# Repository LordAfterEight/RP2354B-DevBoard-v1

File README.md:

# RP2354B-DevBoard-v1
Repository for my first RP2354 based dev board

This dev board comes without external flash and only uses the 2MB of flash that come with the RP2354B chip, thus making this board only compatible with this specific version of the chip.

# Pinout
The two rows of pin headers are simply GPIO 0 - 19 on one side and GPIO 20 - 39 on the other. This means that the ADC pins of the RP2354B can **not** be used on this board as they're simply unconnected.

VBUS is directly connected to the micro-usb connector. 3V3/VSYS is connected to the output of the voltage regulator.

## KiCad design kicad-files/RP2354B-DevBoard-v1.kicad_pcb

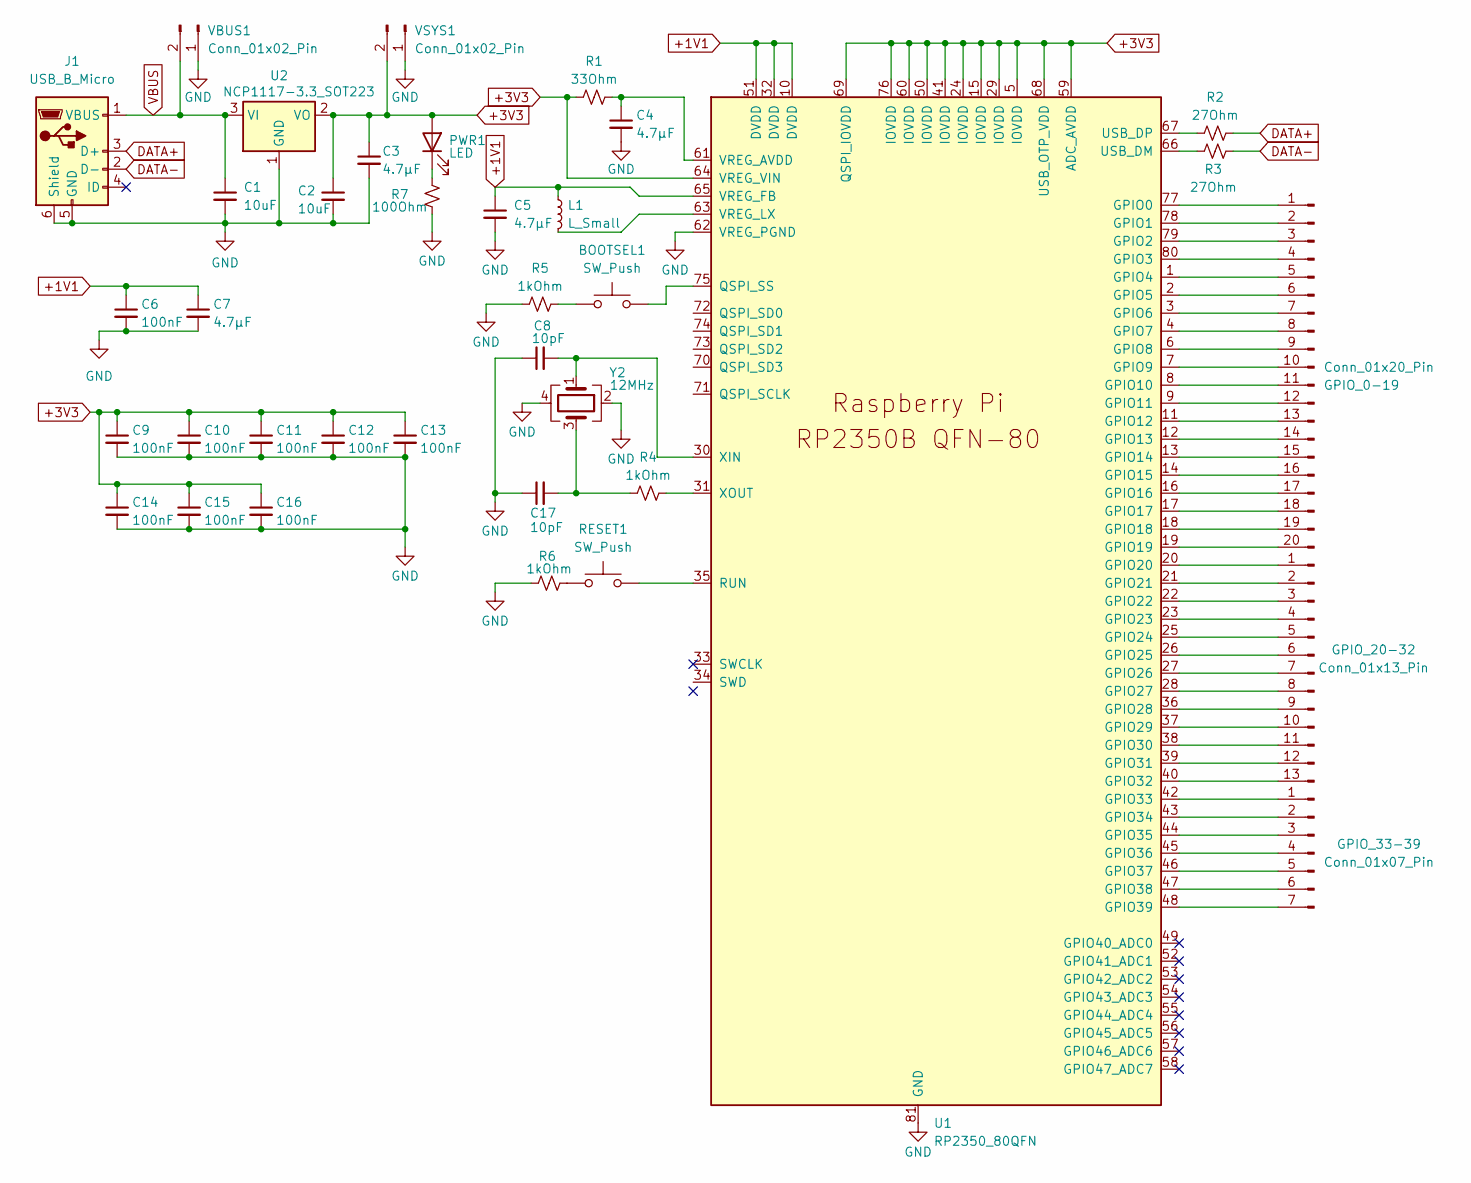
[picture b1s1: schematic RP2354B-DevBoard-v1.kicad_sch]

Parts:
BOOTSEL1: SW_Push; SW_PUSH_6mm
C1, C2: 10uF; C_0402_1005Metric_Pad0.74x0.62mm_HandSolder
C3, C4, C5, C7: 4.7µF; C_0402_1005Metric_Pad0.74x0.62mm_HandSolder
C6, C9, C10, C11, C12, C13, C14, C15, C16: 100nF; C_0402_1005Metric_Pad0.74x0.62mm_HandSolder
C8, C17: 10pF; C_0402_1005Metric_Pad0.74x0.62mm_HandSolder
GPIO_0-19: Conn_01x20_Pin; PinHeader_1x20_P2.54mm_Vertical
GPIO_20-32: Conn_01x13_Pin; PinHeader_1x13_P2.54mm_Vertical
GPIO_33-39: Conn_01x07_Pin; PinHeader_1x07_P2.54mm_Vertical
J1: USB_B_Micro; USB_Micro-B_Amphenol_10103594-0001LF_Horizontal
L1: L_Small; L_Coilcraft_0805HQ_2012Metric
PWR1: LED; LED_0603_1608Metric
R1: 33Ohm; R_0402_1005Metric_Pad0.72x0.64mm_HandSolder
R2, R3: 27Ohm; R_0402_1005Metric_Pad0.72x0.64mm_HandSolder
R4, R5, R6: 1kOhm; R_0402_1005Metric_Pad0.72x0.64mm_HandSolder
R7: 100Ohm; R_0402_1005Metric_Pad0.72x0.64mm_HandSolder
RESET1: SW_Push; SW_PUSH_6mm
U1: RP2350_80QFN; QFN-80-1EP_10x10mm_P0.4mm_EP3.4x3.4mm_ThermalVias
U2: NCP1117-3.3_SOT223; SOT-223-3_TabPin2
VBUS1: Conn_01x02_Pin; PinHeader_1x02_P2.54mm_Vertical
VSYS1: Conn_01x02_Pin; PinHeader_1x02_P2.54mm_Vertical
Y2: 12MHz; Crystal_SMD_EuroQuartz_MJ-4Pin_5.0x3.2mm_HandSoldering

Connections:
+1V1: C5.1, C6.1, C7.1, L1.1, U1.10 (DVDD), U1.32 (DVDD), U1.51 (DVDD), U1.65 (VREG_FB)
+3V3: C2.1, C3.1, C9.1, C10.1, C11.1, C12.1, C13.1, C14.1, C15.1, C16.1, PWR1.2 (A), R1.1, U1.5 (IOVDD), U1.15 (IOVDD), U1.24 (IOVDD), U1.29 (IOVDD), U1.41 (IOVDD), U1.50 (IOVDD), U1.59 (ADC_AVDD), U1.60 (IOVDD), U1.64 (VREG_VIN), U1.68 (USB_OTP_VDD), U1.69 (QSPI_IOVDD), U1.76 (IOVDD), U2.2 (VO), VSYS1.2; also elsewhere on the board
DATA+: J1.3 (D+), R2.2
DATA-: J1.2 (D-), R3.2
GND: C1.2, C2.2, C3.2, C4.2, C5.2, C6.2, C7.2, C8.1, C9.2, C10.2, C11.2, C12.2, C13.2, C14.2, C15.2, C16.2, C17.1, J1.5 (GND), J1.6 (Shield), R5.1, R6.1, R7.1, U1.62 (VREG_PGND), U1.81 (GND), U2.1 (GND), VBUS1.1, VSYS1.1, Y2.2, Y2.4
unnamed 5: BOOTSEL1.1, R5.2; also elsewhere on the board
unnamed: C17.2, R4.1, Y2.3
unnamed: GPIO_0-19.1, U1.77 (GPIO0)
unnamed: GPIO_0-19.2, U1.78 (GPIO1)
unnamed: GPIO_0-19.3, U1.79 (GPIO2)
unnamed: GPIO_0-19.4, U1.80 (GPIO3)
unnamed: GPIO_0-19.5, U1.1 (GPIO4)
unnamed: GPIO_0-19.6, U1.2 (GPIO5)
unnamed: GPIO_0-19.7, U1.3 (GPIO6)
unnamed: GPIO_0-19.8, U1.4 (GPIO7)
unnamed: GPIO_0-19.9, U1.6 (GPIO8)
unnamed: GPIO_0-19.10, U1.7 (GPIO9)
unnamed: GPIO_0-19.11, U1.8 (GPIO10)
unnamed: GPIO_0-19.12, U1.9 (GPIO11)
unnamed: GPIO_0-19.13, U1.11 (GPIO12)
unnamed: GPIO_0-19.14, U1.12 (GPIO13)
unnamed: GPIO_0-19.15, U1.13 (GPIO14)
unnamed: GPIO_0-19.16, U1.14 (GPIO15)
unnamed: GPIO_0-19.17, U1.16 (GPIO16)
unnamed: GPIO_0-19.18, U1.17 (GPIO17)
unnamed: GPIO_0-19.19, U1.18 (GPIO18)
unnamed: GPIO_0-19.20, U1.19 (GPIO19)
unnamed: GPIO_20-32.1, U1.20 (GPIO20)
unnamed: GPIO_20-32.2, U1.21 (GPIO21)
unnamed: GPIO_20-32.3, U1.22 (GPIO22)
unnamed: GPIO_20-32.4, U1.23 (GPIO23)
unnamed: GPIO_20-32.5, U1.25 (GPIO24)
unnamed: GPIO_20-32.6, U1.26 (GPIO25)
unnamed: GPIO_20-32.7, U1.27 (GPIO26)
unnamed: GPIO_20-32.8, U1.28 (GPIO27)
unnamed: GPIO_20-32.9, U1.36 (GPIO28)
unnamed: GPIO_20-32.10, U1.37 (GPIO29)
unnamed: GPIO_20-32.11, U1.38 (GPIO30)
unnamed: GPIO_20-32.12, U1.39 (GPIO31)
unnamed: GPIO_20-32.13, U1.40 (GPIO32)
unnamed: GPIO_33-39.1, U1.42 (GPIO33)
unnamed: GPIO_33-39.2, U1.43 (GPIO34)
unnamed: GPIO_33-39.3, U1.44 (GPIO35)
unnamed: GPIO_33-39.4, U1.45 (GPIO36)
unnamed: GPIO_33-39.5, U1.46 (GPIO37)
unnamed: GPIO_33-39.6, U1.47 (GPIO38)
unnamed: GPIO_33-39.7, U1.48 (GPIO39)
unnamed 47: PWR1.1 (K), R7.2; also elsewhere on the board
unnamed 48: R6.2, RESET1.1; also elsewhere on the board
unnamed 49: BOOTSEL1.2, U1.75 (QSPI_SS); also elsewhere on the board
unnamed 50: RESET1.2, U1.35 (RUN); also elsewhere on the board
unnamed: R3.1, U1.66 (USB_DM)
unnamed: R2.1, U1.67 (USB_DP)
unnamed: C4.1, R1.2, U1.61 (VREG_AVDD)
unnamed: L1.2, U1.63 (VREG_LX)
unnamed: C8.2, U1.30 (XIN), Y2.1
unnamed: R4.2, U1.31 (XOUT)
VBUS: C1.1, J1.1 (VBUS), U2.3 (VI), VBUS1.2

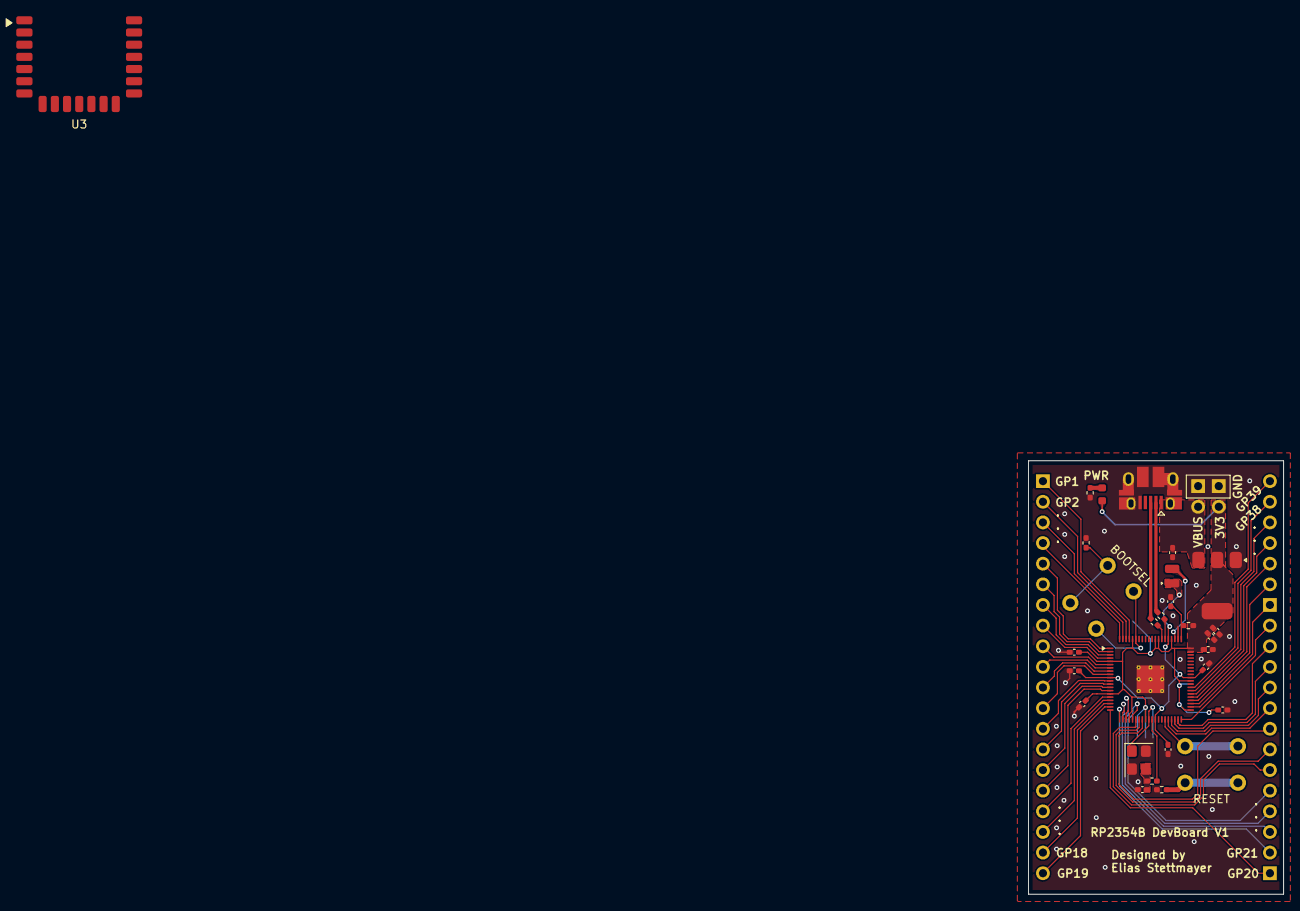
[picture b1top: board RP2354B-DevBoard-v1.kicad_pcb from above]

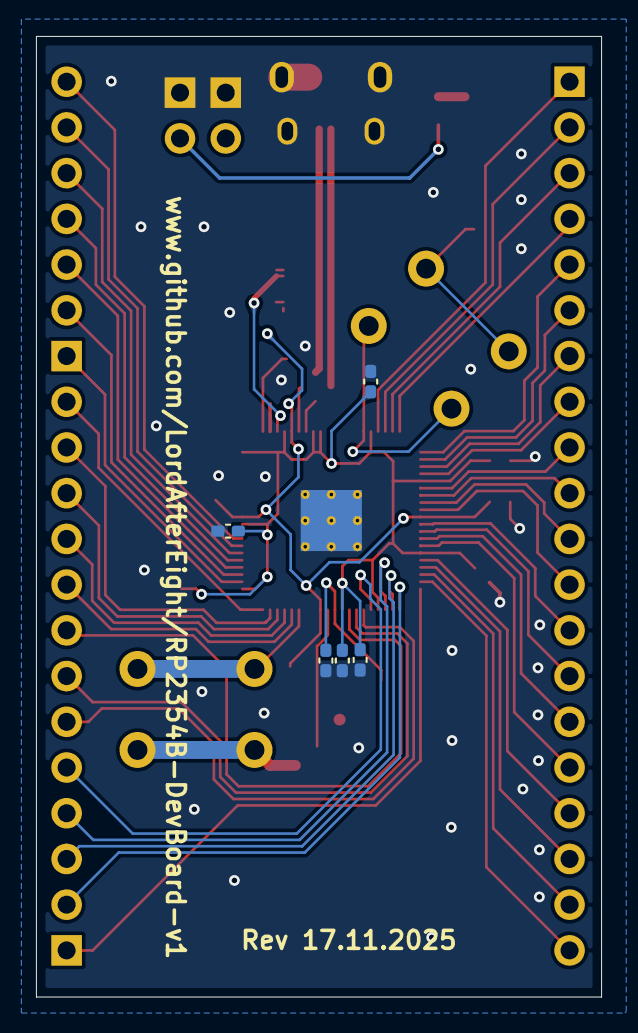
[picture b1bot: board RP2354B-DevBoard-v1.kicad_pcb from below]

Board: 2 copper layers, 31.4 x 53.4 mm, 38 parts (8 on the bottom side), 58 nets.

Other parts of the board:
BOOTSEL: SW_Push; SW_PUSH_6mm_H8mm
PWR: LED; LED_0603_1608Metric
RESET: SW_Push; SW_PUSH_6mm_H8mm
U3: <value>; RMC20452T

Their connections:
+3V3: PWR.2 (A); also elsewhere on the board
unnamed 5: BOOTSEL.1; also elsewhere on the board
unnamed 47: PWR.1 (K); also elsewhere on the board
unnamed 48: RESET.1; also elsewhere on the board
unnamed 49: BOOTSEL.2; also elsewhere on the board
unnamed 50: RESET.2; also elsewhere on the board

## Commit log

2025-11-15 Add KiCad files
2025-11-15 Create KiCad subfolder
2025-11-16 Add images to README
2025-11-17 Replace images in README with new revision
2025-11-17 Update KiCad files to new board revision
2025-11-17 Move updated files to their subfolder
